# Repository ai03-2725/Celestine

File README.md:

# Celestine
A Hi-Tek 725 TKL PCB

#### In light of recent claims that I am 100% liable for any of my open source PCBs, I am adding this disclaimer.
#### I provide these PCBs as a reference for designing keyboard PCBs. Using them within your projects will require a will to do research of one's own and to learn the workings of them, potentially fixing issues if they exist.
# I provide these PCBs without liability and without any guarantees regarding functionality, as expressed in the MIT license under which all of these PCBs are licensed.

This project aims to revive the use of NMB/Hi-Tek 725 series switches, commonly known as "Space Invaders".

Massive credits go to Engicoder, mcmaxmcmc, and many others for helping me along the way with measurements of existing boards and switches.

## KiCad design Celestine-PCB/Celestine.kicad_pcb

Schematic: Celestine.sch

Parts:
C2: 10uF; C_0603
C3, C4, C5: 0.1uF; C_0603
C6: 1uF; C_0603
C7, C8: 22pF; C_0603
D1, D2, D3, D4, D5, D6, D7, D8, D9, D10, D11, D12, D13, D14, D15, D16, D17, D18, D19, D20, D21, D22, D23, D24, D25, D26, D27, D28, D29, D30, D31, D32, D33, D34, D35, D36, D37, D38, D39, D40, D41, D42, D43, D45, D46, D47, D48, D49, D50, D51, D52, D53, D54, D55, D56, D58, D59, D60, D61, D62, D63, D64, D65, D66, D67, D68, D69, D70, D71, D72, D73, D74, D75, D76, D77, D78, D79, D80, D81, D82, D83, D84, D85, D86, D87, D88, D89: SOD-123; D_SOD-123
F1: 500mA; Fuse_SMD1206_Reflow
K_#1, K_#2, K_#3, K_#4, K_#5, K_#6, K_#7, K_#8, K_#9, K_#10: MX-1U; Hitek725-1U
K_'1: MX-1U; Hitek725-1U
K_,1: MX-1U; Hitek725-1U
K_-1: MX-1U; Hitek725-1U
K_.1: MX-1U; Hitek725-1U
K_/1: MX-1U; Hitek725-1U
K_;1: MX-1U; Hitek725-1U
K_=1: MX-1U; Hitek725-1U
K_A1: MX-1U; Hitek725-1U
K_ALT1, K_ALT2: MX-1.5U; Hitek725-1.5U
K_B1: MX-1U; Hitek725-1U
K_BACK1: MX-2U; Hitek725-2U-DudPad
K_C1: MX-1U; Hitek725-1U
K_CAPS1: MX-1.75U; Hitek725-1.75U
K_CTRL1: MX-2U; Hitek725-2U
K_CTRL2: MX-1.5U; Hitek725-1.5U
K_D1: MX-1U; Hitek725-1U
K_DEL1: MX-1U; Hitek725-1U
K_DOWN1: MX-1U; Hitek725-1U
K_E1: MX-1U; Hitek725-1U
K_END1: MX-1U; Hitek725-1U
K_ENTER1: MX-2.25U; Hitek725-2.25U
K_ENTER2: MX-BAE; Hitek725-BigAssEnter-DudPad
K_ESC1: MX-1U; Hitek725-1U
K_F1: MX-1U; Hitek725-1U
K_FN1, K_FN2, K_FN3, K_FN4, K_FN5, K_FN6, K_FN7, K_FN8, K_FN9, K_FN10, K_FN11, K_FN12: MX-1U; Hitek725-1U
K_G1: MX-1U; Hitek725-1U
K_H1: MX-1U; Hitek725-1U
K_HOME1: MX-1U; Hitek725-1U
K_I1: MX-1U; Hitek725-1U
K_INS1: MX-1U; Hitek725-1U
K_J1: MX-1U; Hitek725-1U
K_K1: MX-1U; Hitek725-1U
K_L1: MX-1U; Hitek725-1U
K_LEFT1: MX-1U; Hitek725-1U
K_M1: MX-1U; Hitek725-1U
K_N1: MX-1U; Hitek725-1U
K_O1: MX-1U; Hitek725-1U
K_P1: MX-1U; Hitek725-1U
K_PAUSE1: MX-1U; Hitek725-1U
K_PGDN1: MX-1U; Hitek725-1U
K_PGUP1: MX-1U; Hitek725-1U
K_PRTSC1: MX-1U; Hitek725-1U
K_Q1: MX-1U; Hitek725-1U
K_R1: MX-1U; Hitek725-1U
K_RALT1, K_RALT2: MX-1.5U; Hitek725-1.5U
K_RCTRL1: MX-2U; Hitek725-2U
K_RCTRL2: MX-1.5U; Hitek725-1.5U
K_RIGHT1: MX-1U; Hitek725-1U
K_RSHIFT1: MX-2.75U; Hitek725-2.75U
K_RWIN1: MX-1U; Hitek725-1U
K_S1: MX-1U; Hitek725-1U
K_SBACK1: MX-1U; Hitek725-1U
K_SBACK2: MX-1U; Hitek725-1U-DudPad
K_SHIFT1: MX-2.25U; Hitek725-2.25U
K_SLCK1: MX-1U; Hitek725-1U
K_SPACE1: MX-7U; Hitek725-7U
K_T1: MX-1U; Hitek725-1U
K_TAB1: MX-1.5U; Hitek725-1.5U
K_U1: MX-1U; Hitek725-1U
K_UP1: MX-1U; Hitek725-1U
K_V1: MX-1U; Hitek725-1U
K_W1: MX-1U; Hitek725-1U
K_WIN1: MX-1U; Hitek725-1U
K_X1: MX-1U; Hitek725-1U
K_Y1: MX-1U; Hitek725-1U
K_Z1: MX-1U; Hitek725-1U
K_[1: MX-1U; Hitek725-1U
K_\1: MX-1.5U; Hitek725-1.5U
K_]1: MX-1U; Hitek725-1U
K_`1: MX-1U; Hitek725-1U
R67, R68: 22; R_0805
R70: 10k; R_0805
R71: 1k; R_0805
R73, R74: 5.1k; R_0805
SW1: SW_Push; SKQG-1155865
U1: ATmega32U4-AU; TQFP-44_10x10mm_Pitch0.8mm
U2: PRTR5V0U2X; SOT143B
USB1: HRO-TYPE-C-31-M-12; HRO-TYPE-C-31-M-12-Assembly
Y1: 16Mhz; Crystal_SMD_3225-4pin_3.2x2.5mm

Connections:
COL0: K_CAPS1.1, K_CTRL1.1, K_CTRL2.2, K_ESC1.1, K_SHIFT1.1, K_TAB1.1, K_`1.1, U1.26 (PD6)
COL1: K_#1.1, K_A1.1, K_Q1.1, K_WIN1.1, U1.27 (PD7)
COL2: K_#2.1, K_ALT1.1, K_ALT2.2, K_FN1.1, K_S1.1, K_W1.1, K_Z1.1, U1.28 (PB4)
COL3: K_#3.1, K_D1.1, K_E1.1, K_FN2.1, K_X1.1, U1.29 (PB5)
COL4: K_#4.1, K_C1.1, K_F1.1, K_FN3.1, K_R1.1, U1.30 (PB6)
COL5: K_#5.1, K_FN4.1, K_G1.1, K_T1.1, K_V1.1, U1.31 (PC6)
COL6: K_#6.1, K_B1.1, K_FN5.1, K_H1.1, K_Y1.1, U1.32 (PC7)
COL7: K_#7.1, K_FN6.1, K_J1.1, K_N1.1, K_SPACE1.1, K_U1.1, U1.36 (PF7)
COL8: K_#8.1, K_FN7.1, K_I1.1, K_K1.1, K_M1.1, U1.37 (PF6)
COL9: K_#9.1, K_,1.1, K_FN8.1, K_L1.1, K_O1.1, U1.38 (PF5)
COL10: K_#10.1, K_.1.1, K_;1.1, K_FN9.1, K_P1.1, U1.39 (PF4)
COL11: K_'1.1, K_-1.1, K_/1.1, K_FN10.1, K_RALT1.1, K_RALT2.2, K_[1.1, U1.40 (PF1)
COL12: K_=1.1, K_FN11.1, K_RSHIFT1.1, K_RWIN1.1, K_]1.1, U1.41 (PF0)
COL13: K_BACK1.2, K_ENTER1.1, K_ENTER2.2, K_FN12.1, K_RCTRL1.1, K_RCTRL2.2, K_SBACK1.1, K_SBACK2.1, K_\1.1, U1.25 (PD4)
COL14: K_DEL1.1, K_INS1.1, K_LEFT1.1, K_PRTSC1.1, U1.22 (PD5)
COL15: K_DOWN1.1, K_END1.1, K_HOME1.1, K_SLCK1.1, K_UP1.1, U1.21 (PD3)
COL16: K_PAUSE1.1, K_PGDN1.1, K_PGUP1.1, K_RIGHT1.1, U1.20 (PD2)
D+: R68.1, U1.4 (D+)
D-: R67.1, U1.3 (D-)
GND: C2.1, C3.1, C4.1, C5.1, C6.2, C7.2, C8.2, R71.1, R73.1, R74.1, SW1.1, U1.5 (UGND), U1.15 (GND), U1.23 (GND), U1.35 (GND), U1.43 (GND), U2.1, USB1.1, USB1.12, USB1.13, Y1.2, Y1.4
unnamed: C6.1, U1.6 (UCAP)
unnamed: C7.1, U1.17 (XTAL1), Y1.1
unnamed: C8.1, U1.16 (XTAL2), Y1.3
unnamed: D1.2, K_`1.2
unnamed: D2.2, K_#1.2
unnamed: D3.2, K_#2.2
unnamed: D4.2, K_#3.2
unnamed: D5.2, K_#4.2
unnamed: D6.2, K_#5.2
unnamed: D7.2, K_#6.2
unnamed: D8.2, K_#7.2
unnamed: D9.2, K_#8.2
unnamed: D10.2, K_#9.2
unnamed: D11.2, K_#10.2
unnamed: D12.2, K_-1.2
unnamed: D13.2, K_=1.2
unnamed: D14.2, K_BACK1.1, K_SBACK1.2
unnamed: D15.2, K_ESC1.2
unnamed: D16.2, K_TAB1.2
unnamed: D17.2, K_Q1.2
unnamed: D18.2, K_W1.2
unnamed: D19.2, K_E1.2
unnamed: D20.2, K_R1.2
unnamed: D21.2, K_T1.2
unnamed: D22.2, K_Y1.2
unnamed: D23.2, K_U1.2
unnamed: D24.2, K_I1.2
unnamed: D25.2, K_O1.2
unnamed: D26.2, K_P1.2
unnamed: D27.2, K_[1.2
unnamed: D28.2, K_]1.2
unnamed: D29.2, K_\1.2
unnamed: D30.2, K_FN1.2
unnamed: D31.2, K_CAPS1.2
unnamed: D32.2, K_A1.2
unnamed: D33.2, K_S1.2
unnamed: D34.2, K_D1.2
unnamed: D35.2, K_F1.2
unnamed: D36.2, K_G1.2
unnamed: D37.2, K_H1.2
unnamed: D38.2, K_J1.2
unnamed: D39.2, K_K1.2
unnamed: D40.2, K_L1.2
unnamed: D41.2, K_;1.2
unnamed: D42.2, K_'1.2
unnamed: D43.2, K_ENTER1.2
unnamed: D45.2, K_SHIFT1.2
unnamed: D46.2, K_Z1.2
unnamed: D47.2, K_X1.2
unnamed: D48.2, K_C1.2
unnamed: D49.2, K_V1.2
unnamed: D50.2, K_B1.2
unnamed: D51.2, K_N1.2
unnamed: D52.2, K_M1.2
unnamed: D53.2, K_,1.2
unnamed: D54.2, K_.1.2
unnamed: D55.2, K_/1.2
unnamed: D56.2, K_RSHIFT1.2
unnamed: D58.2, K_FN2.2
unnamed: D59.2, K_CTRL1.2, K_CTRL2.1
unnamed: D60.2, K_FN3.2
unnamed: D61.2, K_SPACE1.2
unnamed: D62.2, K_FN4.2
unnamed: D63.2, K_FN5.2
unnamed: D64.2, K_RALT1.2, K_RALT2.1
unnamed: D65.2, K_RCTRL1.2, K_RCTRL2.1
unnamed: D66.2, K_FN6.2
unnamed: D67.2, K_ALT1.2, K_ALT2.1
unnamed: D68.2, K_SBACK2.2
unnamed: D69.2, K_FN7.2
unnamed: D70.2, K_FN8.2
unnamed: D71.2, K_FN9.2
unnamed: D72.2, K_FN10.2
unnamed: D73.2, K_FN11.2
unnamed: D74.2, K_FN12.2
unnamed: D75.2, K_WIN1.2
unnamed: D76.2, K_RWIN1.2
unnamed: D77.2, K_PRTSC1.2
unnamed: D78.2, K_SLCK1.2
unnamed: D79.2, K_PAUSE1.2
unnamed: D80.2, K_INS1.2
unnamed: D81.2, K_HOME1.2
unnamed: D82.2, K_PGUP1.2
unnamed: D83.2, K_DEL1.2
unnamed: D84.2, K_END1.2
unnamed: D85.2, K_PGDN1.2
unnamed: D86.2, K_UP1.2
unnamed: D87.2, K_LEFT1.2
unnamed: D88.2, K_DOWN1.2
unnamed: D89.2, K_RIGHT1.2
unnamed: R67.2, U2.3, USB1.5, USB1.7
unnamed: R68.2, U2.2, USB1.6, USB1.8
unnamed: R70.2, SW1.2, U1.13 (~RESET)
unnamed: R71.2, U1.33 (~HWB~/PE2)
unnamed: R73.2, USB1.4
unnamed: R74.2, USB1.10
ROW0: D15.1, D30.1, D58.1, D60.1, D62.1, D63.1, D66.1, D69.1, D70.1, D71.1, D72.1, D73.1, D74.1, D77.1, D78.1, D79.1, U1.9 (PB1)
ROW1: D1.1, D2.1, D3.1, D4.1, D5.1, D6.1, D7.1, D8.1, D9.1, D10.1, D11.1, D12.1, D13.1, D14.1, D80.1, D81.1, D82.1, U1.10 (PB2)
ROW2: D16.1, D17.1, D18.1, D19.1, D20.1, D21.1, D22.1, D23.1, D24.1, D25.1, D26.1, D27.1, D28.1, D29.1, D83.1, D84.1, D85.1, U1.11 (PB3)
ROW3: D31.1, D32.1, D33.1, D34.1, D35.1, D36.1, D37.1, D38.1, D39.1, D40.1, D41.1, D42.1, D43.1, U1.12 (PB7)
ROW4: D45.1, D46.1, D47.1, D48.1, D49.1, D50.1, D51.1, D52.1, D53.1, D54.1, D55.1, D56.1, D68.1, D86.1, U1.18 (PD0)
ROW5: D59.1, D61.1, D64.1, D65.1, D67.1, D75.1, D76.1, D87.1, D88.1, D89.1, U1.19 (PD1)
VCC: F1.2, U2.4, USB1.2, USB1.11

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
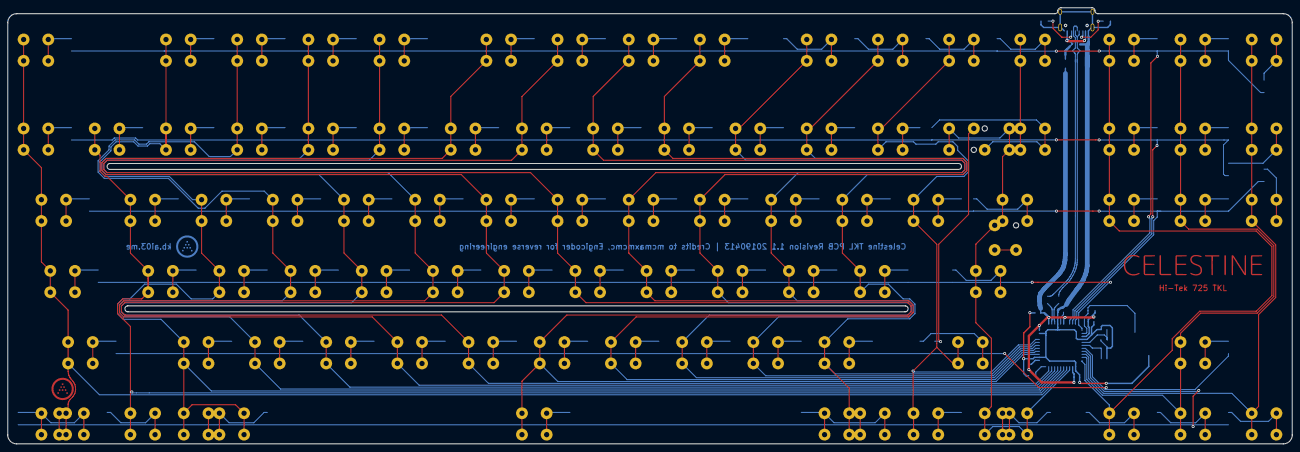
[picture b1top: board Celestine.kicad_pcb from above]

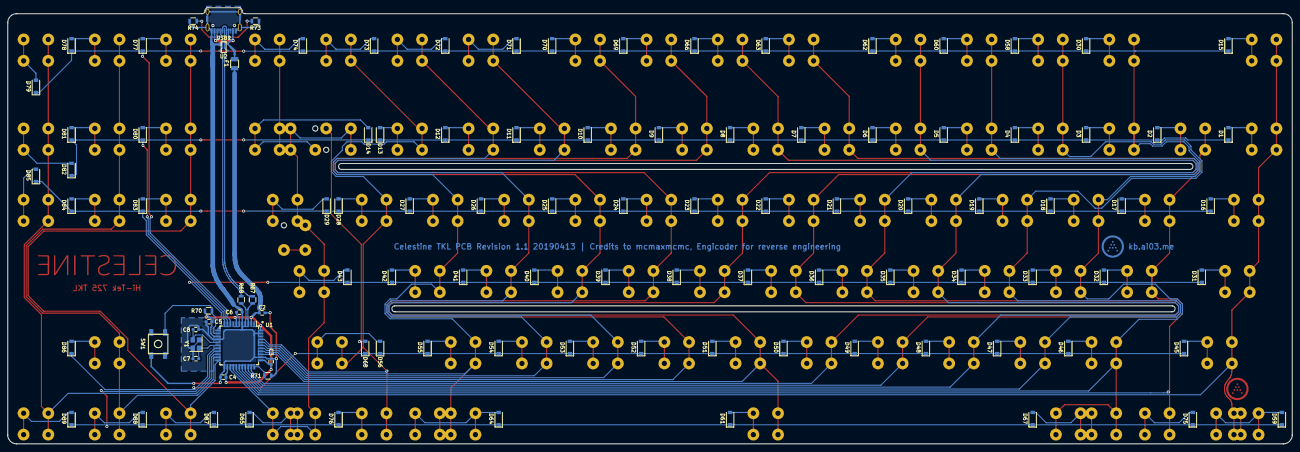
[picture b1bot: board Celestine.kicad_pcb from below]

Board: 2 copper layers, 343.7 x 116.7 mm, 199 parts (106 on the bottom side), 124 nets.

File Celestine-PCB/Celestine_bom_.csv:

Component,Description,Part,References,Value,Footprint,Quantity Per PCB
1,Capacitor,C_Small,C3 C4 C5,0.1uF,C_0603,3
2,Capacitor,C_Small,C2,10uF,C_0603,1
3,Capacitor,C_Small,C6,1uF,C_0603,1
4,Capacitor,C_Small,C7 C8,22pF,C_0603,2
5,"Diode, Generic",D_Small,D1 D2 D3 D4 D5 D6 D7 D8 D9 D10 D11 D12 D13 D14 D15 D16 D17 D18 D19 D20 D21 D22 D23 D24 D25 D26 D27 D28 D29 D30 D31 D32 D33 D34 D35 D36 D37 D38 D39 D40 D41 D42 D43 D45 D46 D47 D48 D49 D50 D51 D52 D53 D54 D55 D56 D58 D59 D60 D61 D62 D63 D64 D65 D66 D67 D68 D69 D70 D71 D72 D73 D74 D75 D76 D77 D78 D79 D80 D81 D82 D83 D84 D85 D86 D87 D88 D89,SOD-123,D_SOD-123,87
6,"Polyfuse, 500mA hold, 1A trip",Polyfuse_Small,F1,500mA,Fuse_SMD1206_Reflow,1
7,Resistor,R_Small,R70,10k,R_0805,1
8,Resistor,R_Small,R71,1k,R_0805,1
9,Resistor,R_Small,R67 R68,22,R_0805,2
10,Resistor,R_Small,R73 R74,5.1k,R_0805,2
11,"Push button, SMT, 5.2 x 5.2mm",SW_Push,SW1,SW_Push,SKQG-1155865,1
12,"Microcontroller, ATmega32u4-AU",ATmega32U4-AU,U1,ATmega32U4-AU,TQFP-44_10x10mm_Pitch0.8mm,1
13,ESD Protection Chip,PRTR5V0U2X,U2,PRTR5V0U2X,SOT143B,1
14,USB Type-C Connector,HRO-TYPE-C-31-M-12,USB1,HRO-TYPE-C-31-M-12,HRO-TYPE-C-31-M-12-Assembly,1
15,"Crystal, SMT, 3.2 x 2.5mm, 4 pads",Crystal_GND24,Y1,16Mhz,Crystal_SMD_3225-4pin_3.2x2.5mm,1
,,,,,,
,,,,,,
,,,,,,
,,,,,,
,,,,,,
Component Groups:,15,,,,,
Component Count:,106,,,,,
Fitted Components:,106,,,,,
Number of PCBs:,1,,,,,
Total components:,106,,,,,
Schematic Version:,,,,,,
Schematic Date:,,,,,,
BoM Date:,1/11/2019 0:30,,,,,
Schematic Source:,,,,,,
KiCad Version:,Eeschema (5.0.0),,,,,

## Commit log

2019-01-07 Add submodules, make footprint
2019-01-09 Add submodules
2019-01-09 Begin work
2019-01-09 Update submodules
2019-01-09 Remove submodule
2019-01-09 Begin add libraries
2019-01-09 Add footprint libs
2019-01-09 Bind some footprints
2019-01-09 New footprint data by Engicoder
2019-01-09 Make a few sizes of the footprint
2019-01-09 Build generic schematic
2019-01-10 Build the PCB
2019-01-11 Remove need for jumpers
2019-01-11 Generate production data
2019-01-11 Clean BOM
2019-01-11 Generate sandwich case
2019-01-11 Rename gerbers
2019-05-27 Progress
